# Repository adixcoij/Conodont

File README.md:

# Conodont
Neovim のために設計したキーボードです。
Neovimで使用するキーを重点的に配置しています。
## 使用ソフト
Kicad 7.0
Qmk farmware
## 一から自作キーボード
自作キーボードを作ったことのある人は一回は夢見る基盤から自作キーボードについて詰まった点が多々あったのでメモとして残したいと思います。
## 初めに
自分はKicadを使ったことがなかったので、間違った点があるかも知れませんが基板は発注出来たので
多めに見てください。
## Kicadについて
Kicadに入門する一番の登竜門は自作キーボードが適切な選択肢です。回路としても抵抗を使わない為、計算を行う必要がなく
電圧を気にする事なく回路を作成できます。
またブレットボードだと何処を間違えたかわかりにくいですが、基盤を発注すればまず相手側が間違えることはないため原因の特定が容易です。
（失敗した時、値段はお高くつきますがKicadが検知してくれるためミスは最小限で済みます）
## Kicadのワークフロー
前例と必要部品の下調べ

↓

Kicadでの回路図の作成　←難しそうに見えて一番簡単

↓

Kicadでのレイアウトの作成

↓

基盤発注の最終設定

この中では前例の下調べと基盤発注が難しいと思います。

## Kicadでの回路図の作成
## Kicadでのレイアウトの作成
## 基盤発注
## 参考文献

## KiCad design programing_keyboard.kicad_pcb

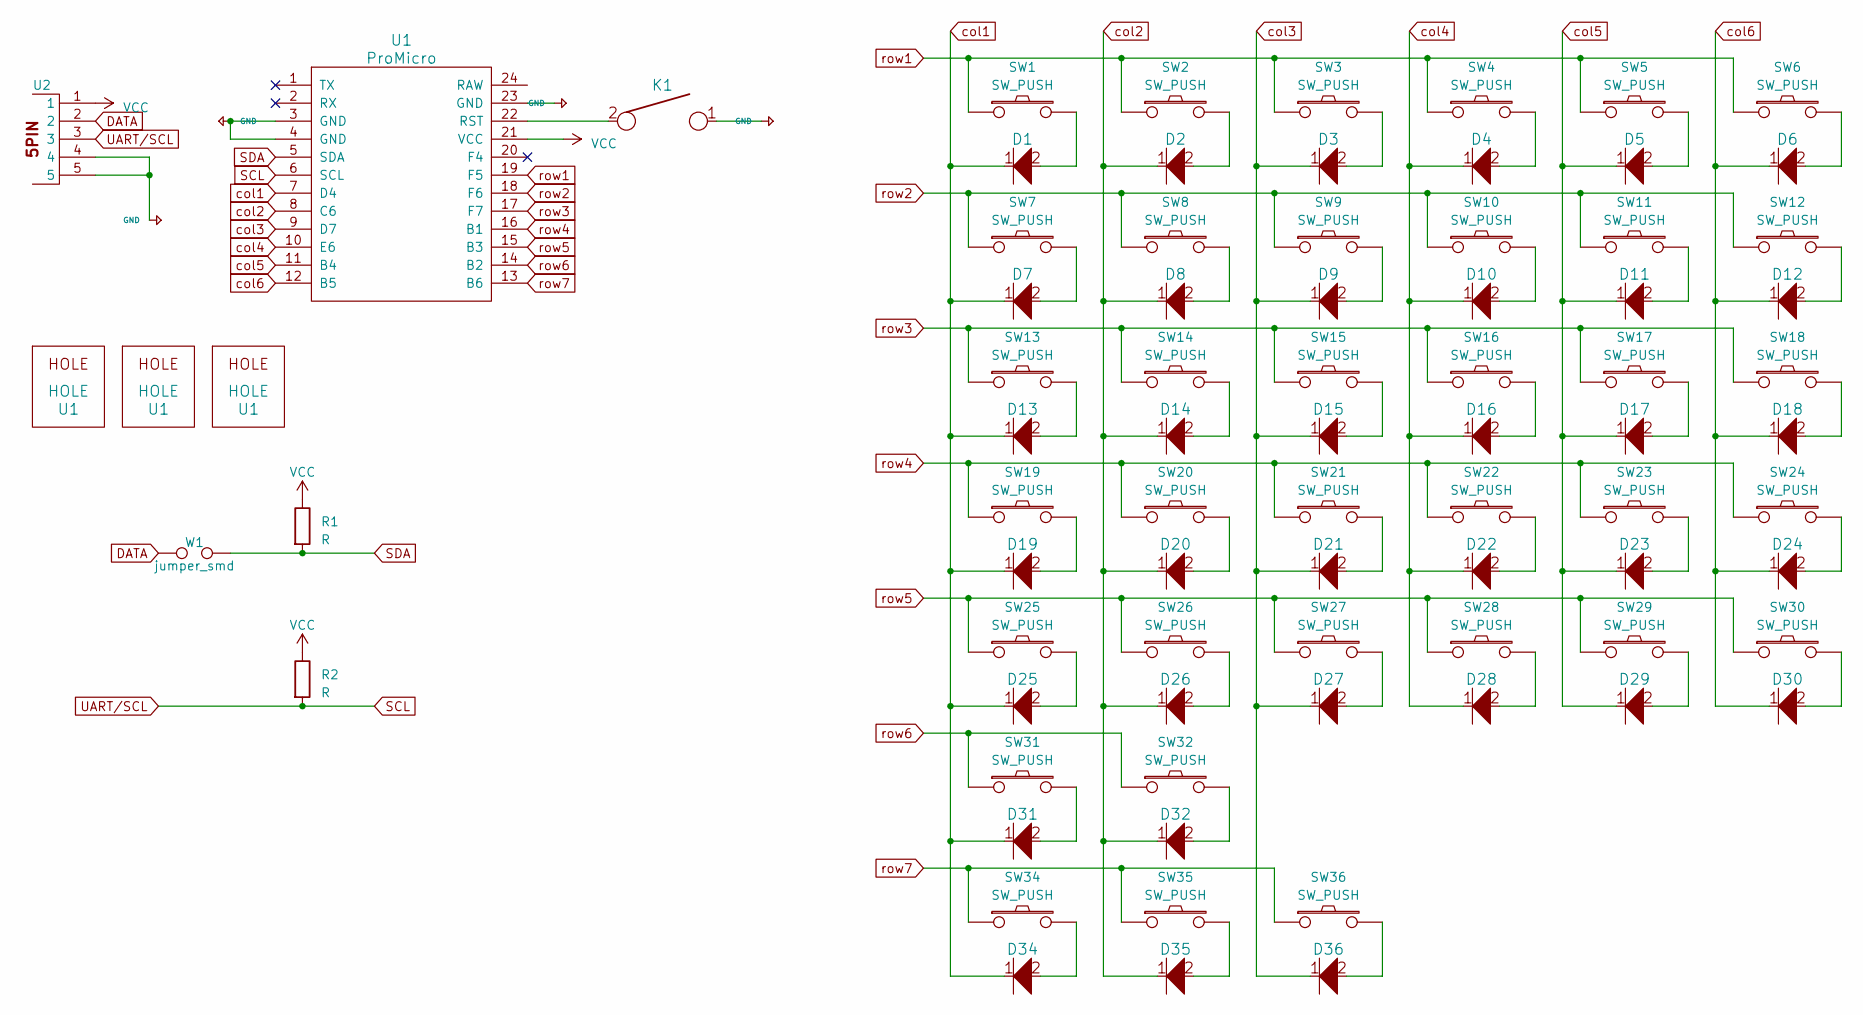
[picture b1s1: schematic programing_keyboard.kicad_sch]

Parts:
D1, D2, D3, D4, D5, D6, D7, D8, D9, D10, D11, D12, D13, D14, D15, D16, D17, D18, D19, D20, D21, D22, D23, D24, D25, D26, D27, D28, D29, D30, D31, D32, D34, D35, D36: D; Diode_SMD_THT
K1: KEYSW; tact_switch
R1, R2: R; R_Axial_DIN0207_L6.3mm_D2.5mm_P10.16mm_Horizontal
SW1, SW2, SW3, SW4, SW5, SW6, SW7, SW8, SW9, SW10, SW11, SW12, SW13, SW14, SW15, SW16, SW17, SW18, SW19, SW20, SW21, SW22, SW23, SW24, SW27, SW28, SW29, SW30, SW31, SW34, SW35, SW36: SW_PUSH; key_switch
SW25: SW_PUSH; key_switch_150
SW26, SW32: SW_PUSH; key_switch_200
U1: HOLE; hole
U2: trrs_jack
W1: jumper_smd; jumper_smd_2dub

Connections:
+5V: K1.1, U1.3 (GND), U1.4 (GND), U1.23 (GND), U2.4, U2.5
DATA: U2.2, W1.1
unnamed: D1.2, SW1.2
unnamed: D2.2, SW2.2
unnamed: D3.2, SW3.2
unnamed: D4.2, SW4.2
unnamed: D5.2, SW5.2
unnamed: D6.2, SW6.2
unnamed: D7.2, SW7.2
unnamed: D8.2, SW8.2
unnamed: D9.2, SW9.2
unnamed: D10.2, SW10.2
unnamed: D11.2, SW11.2
unnamed: D12.2, SW12.2
unnamed: D13.2, SW13.2
unnamed: D14.2, SW14.2
unnamed: D15.2, SW15.2
unnamed: D16.2, SW16.2
unnamed: D17.2, SW17.2
unnamed: D18.2, SW18.2
unnamed: D19.2, SW19.2
unnamed: D20.2, SW20.2
unnamed: D21.2, SW21.2
unnamed: D22.2, SW22.2
unnamed: D23.2, SW23.2
unnamed: D24.2, SW24.2
unnamed: D25.2, SW25.2
unnamed: D26.2, SW26.2
unnamed: D27.2, SW27.2
unnamed: D28.2, SW28.2
unnamed: D29.2, SW29.2
unnamed: D30.2, SW30.2
unnamed: D31.2, SW31.2
unnamed: D32.2, SW32.2
unnamed: D34.2, SW34.2
unnamed: D35.2, SW35.2
unnamed: D36.2, SW36.2
unnamed: K1.2, U1.22 (RST)
SCL: R2.2, U1.6 (SCL), U2.3
SDA: R1.2, U1.5 (SDA), W1.2
VCC: R1.1, R2.1, U1.21 (VCC), U2.1
col1: D1.1, D7.1, D13.1, D19.1, D25.1, D31.1, D34.1, U1.7 (D4)
col2: D2.1, D8.1, D14.1, D20.1, D26.1, D32.1, D35.1, U1.8 (C6)
col3: D3.1, D9.1, D15.1, D21.1, D27.1, D36.1, U1.9 (D7)
col4: D4.1, D10.1, D16.1, D22.1, D28.1, U1.10 (E6)
col5: D5.1, D11.1, D17.1, D23.1, D29.1, U1.11 (B4)
col6: D6.1, D12.1, D18.1, D24.1, D30.1, U1.12 (B5)
row1: SW1.1, SW2.1, SW3.1, SW4.1, SW5.1, SW6.1, U1.19 (F5)
row2: SW7.1, SW8.1, SW9.1, SW10.1, SW11.1, SW12.1, U1.18 (F6)
row3: SW13.1, SW14.1, SW15.1, SW16.1, SW17.1, SW18.1, U1.17 (F7)
row4: SW19.1, SW20.1, SW21.1, SW22.1, SW23.1, SW24.1, U1.16 (B1)
row5: SW25.1, SW26.1, SW27.1, SW28.1, SW29.1, SW30.1, U1.15 (B3)
row6: SW31.1, SW32.1, U1.14 (B2)
row7: SW34.1, SW35.1, SW36.1, U1.13 (B6)

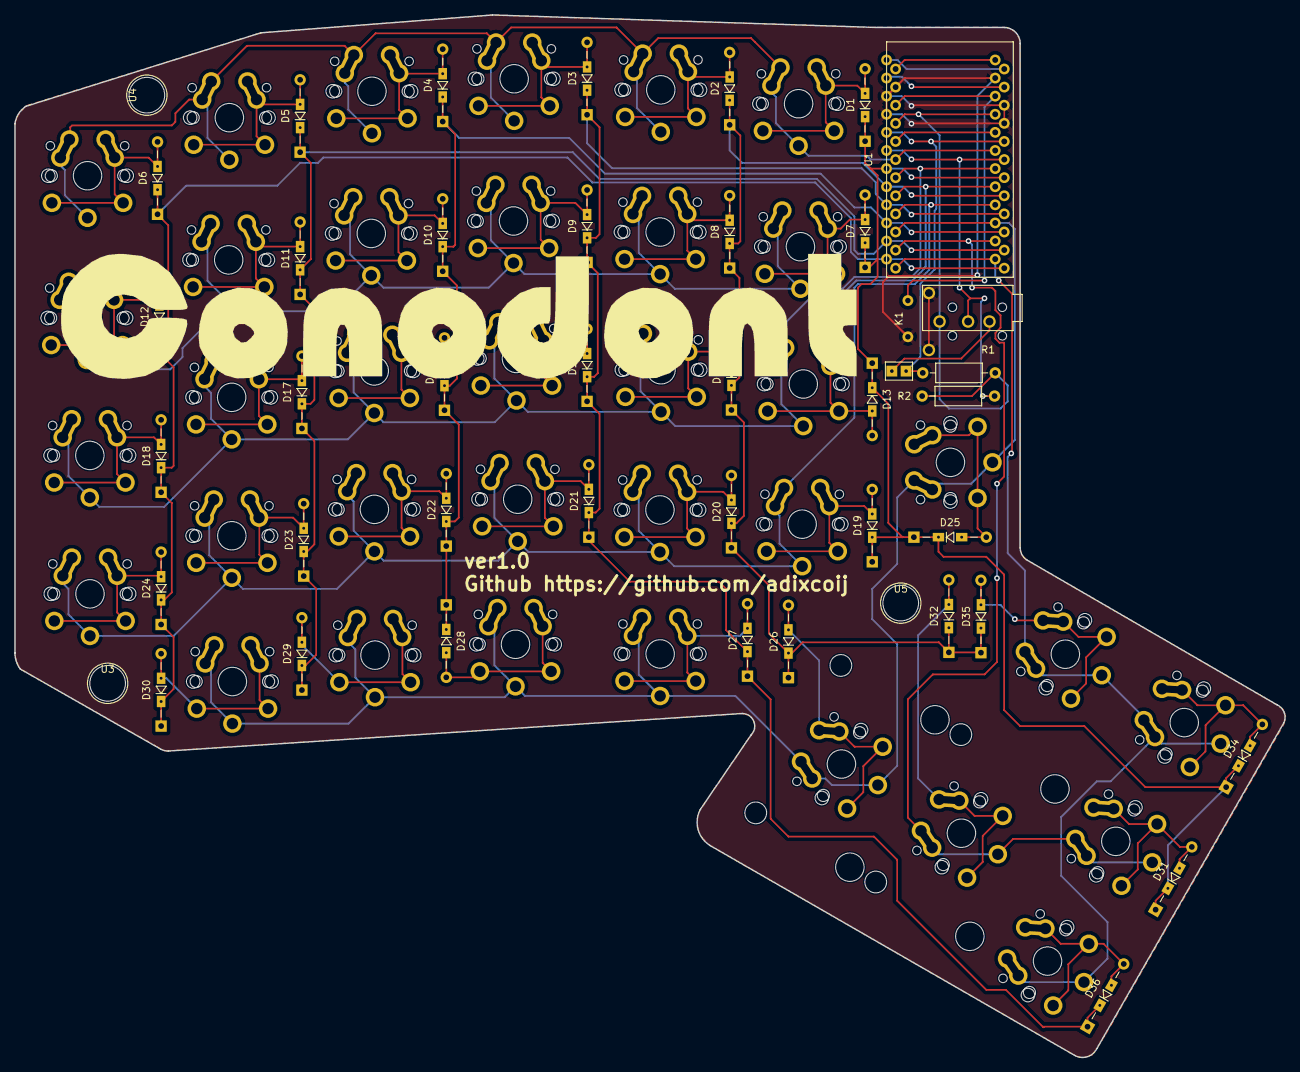
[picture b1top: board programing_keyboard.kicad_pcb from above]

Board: 2 copper layers, 178.2 x 146.2 mm, 79 parts (0 on the bottom side), 54 nets.

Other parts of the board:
U3, U4, U5: HOLE; hole

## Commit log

2023-03-15 test
2023-03-15 test2
2023-03-31 説明文の追加
2023-03-31 大きさやデータの変更
2023-04-09 qmkの更新
2023-04-10 README.md を更新
